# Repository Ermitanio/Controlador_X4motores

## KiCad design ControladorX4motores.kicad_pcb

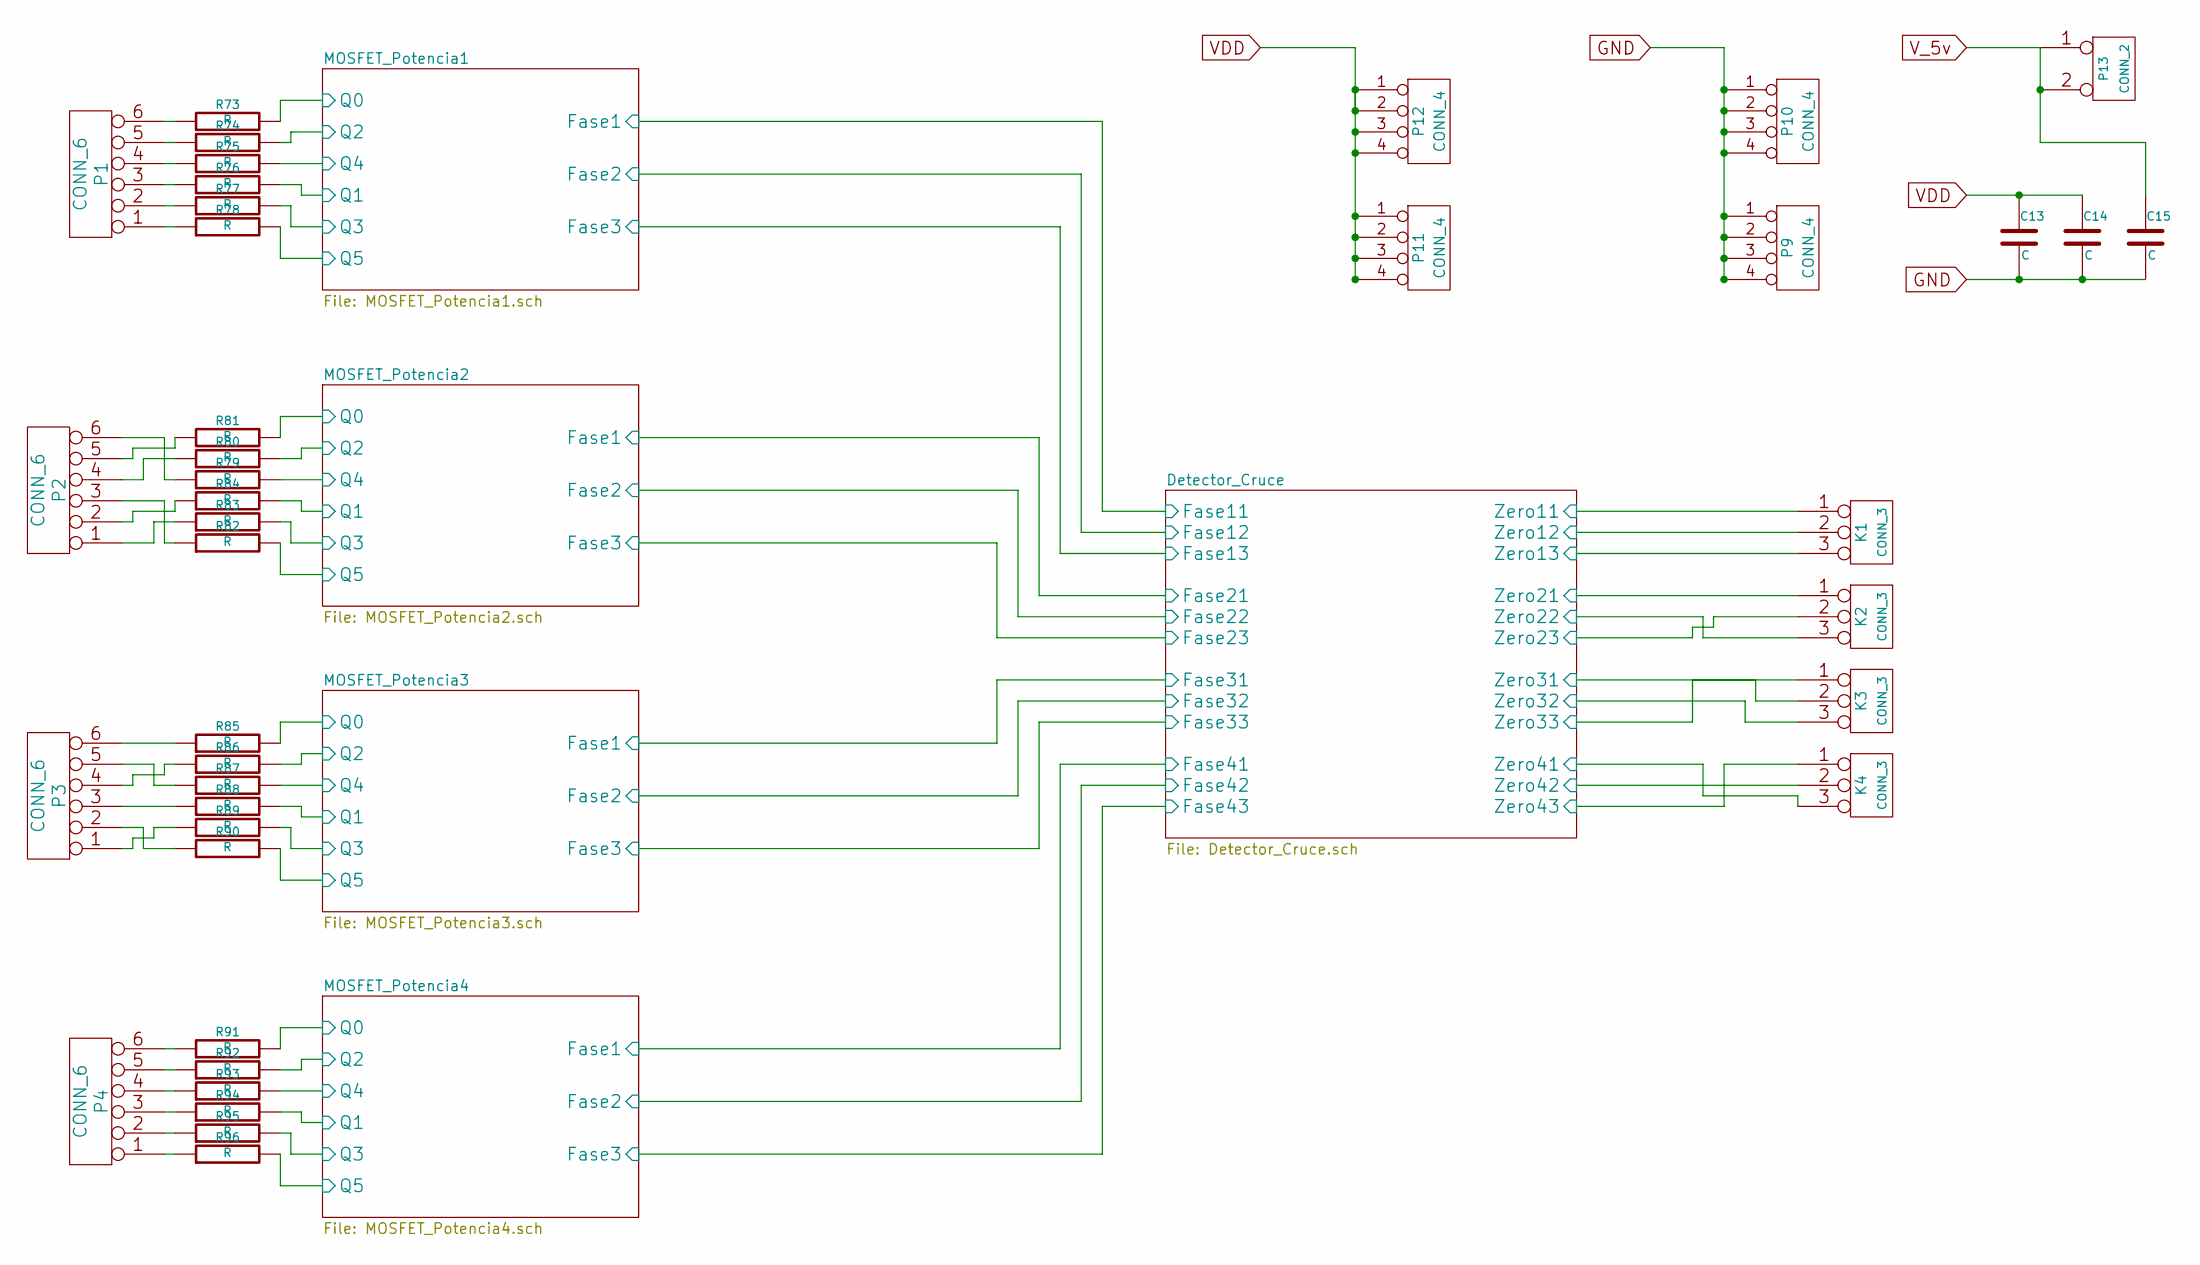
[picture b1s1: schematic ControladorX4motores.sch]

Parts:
C13, C14, C15: C
K1, K2, K3, K4: CONN_3
P1, P2, P3, P4: CONN_6
P9, P10, P11, P12: CONN_4
P13: CONN_2
R73, R74, R75, R76, R77, R78, R79, R80, R81, R82, R83, R84, R85, R86, R87, R88, R89, R90, R91, R92, R93, R94, R95, R96: R

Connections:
/Detector_Cruce/Zero11: K1.1; also elsewhere on the board
/Detector_Cruce/Zero12: K1.2 (PM); also elsewhere on the board
/Detector_Cruce/Zero13: K1.3; also elsewhere on the board
/Detector_Cruce/Zero21: K2.1; also elsewhere on the board
/Detector_Cruce/Zero22: K2.3; also elsewhere on the board
/Detector_Cruce/Zero23: K2.2 (PM); also elsewhere on the board
/Detector_Cruce/Zero31: K3.2 (PM); also elsewhere on the board
/Detector_Cruce/Zero32: K3.3; also elsewhere on the board
/Detector_Cruce/Zero33: K3.1; also elsewhere on the board
/Detector_Cruce/Zero41: K4.3; also elsewhere on the board
/Detector_Cruce/Zero42: K4.2 (PM); also elsewhere on the board
/Detector_Cruce/Zero43: K4.1; also elsewhere on the board
/MOSFET_Potencia1/Q0: R73.2; also elsewhere on the board
/MOSFET_Potencia1/Q1: R76.2; also elsewhere on the board
/MOSFET_Potencia1/Q2: R74.2; also elsewhere on the board
/MOSFET_Potencia1/Q3: R77.2; also elsewhere on the board
/MOSFET_Potencia1/Q4: R75.2; also elsewhere on the board
/MOSFET_Potencia1/Q5: R78.2; also elsewhere on the board
/MOSFET_Potencia2/Q0: R81.2; also elsewhere on the board
/MOSFET_Potencia2/Q1: R84.2; also elsewhere on the board
/MOSFET_Potencia2/Q2: R80.2; also elsewhere on the board
/MOSFET_Potencia2/Q3: R83.2; also elsewhere on the board
/MOSFET_Potencia2/Q4: R79.2; also elsewhere on the board
/MOSFET_Potencia2/Q5: R82.2; also elsewhere on the board
/MOSFET_Potencia3/Q0: R85.2; also elsewhere on the board
/MOSFET_Potencia3/Q1: R88.2; also elsewhere on the board
/MOSFET_Potencia3/Q2: R86.2; also elsewhere on the board
/MOSFET_Potencia3/Q3: R89.2; also elsewhere on the board
/MOSFET_Potencia3/Q4: R87.2; also elsewhere on the board
/MOSFET_Potencia3/Q5: R90.2; also elsewhere on the board
/MOSFET_Potencia4/Q0: R91.2; also elsewhere on the board
/MOSFET_Potencia4/Q1: R94.2; also elsewhere on the board
/MOSFET_Potencia4/Q2: R92.2; also elsewhere on the board
/MOSFET_Potencia4/Q3: R95.2; also elsewhere on the board
/MOSFET_Potencia4/Q4: R93.2; also elsewhere on the board
/MOSFET_Potencia4/Q5: R96.2; also elsewhere on the board
GND: C13.2, C14.2, C15.2, P9.1, P9.2, P9.3, P9.4, P10.1, P10.2, P10.3, P10.4; also elsewhere on the board
unnamed: P4.1, R96.1
unnamed: P4.2, R95.1
unnamed: P4.3, R94.1
unnamed: P4.4, R93.1
unnamed: P4.5, R92.1
unnamed: P4.6, R91.1
unnamed: P3.2, R90.1
unnamed: P3.3, R88.1
unnamed: P3.6, R85.1
unnamed: P1.1, R78.1
unnamed: P1.2, R77.1
unnamed: P1.3, R76.1
unnamed: P1.4, R75.1
unnamed: P1.5, R74.1
unnamed: P1.6, R73.1
unnamed: P3.5, R87.1
unnamed: P3.1, R89.1
unnamed: P3.4, R86.1
unnamed: P2.1, R83.1
unnamed: P2.2, R84.1
unnamed: P2.6, R79.1
unnamed: P2.3, R82.1
unnamed: P2.4, R80.1
unnamed: P2.5, R81.1
VDD: C13.1, C14.1, P11.1, P11.2, P11.3, P11.4, P12.1, P12.2, P12.3, P12.4; also elsewhere on the board
V_5v: C15.1, P13.1, P13.2 (PM); also elsewhere on the board

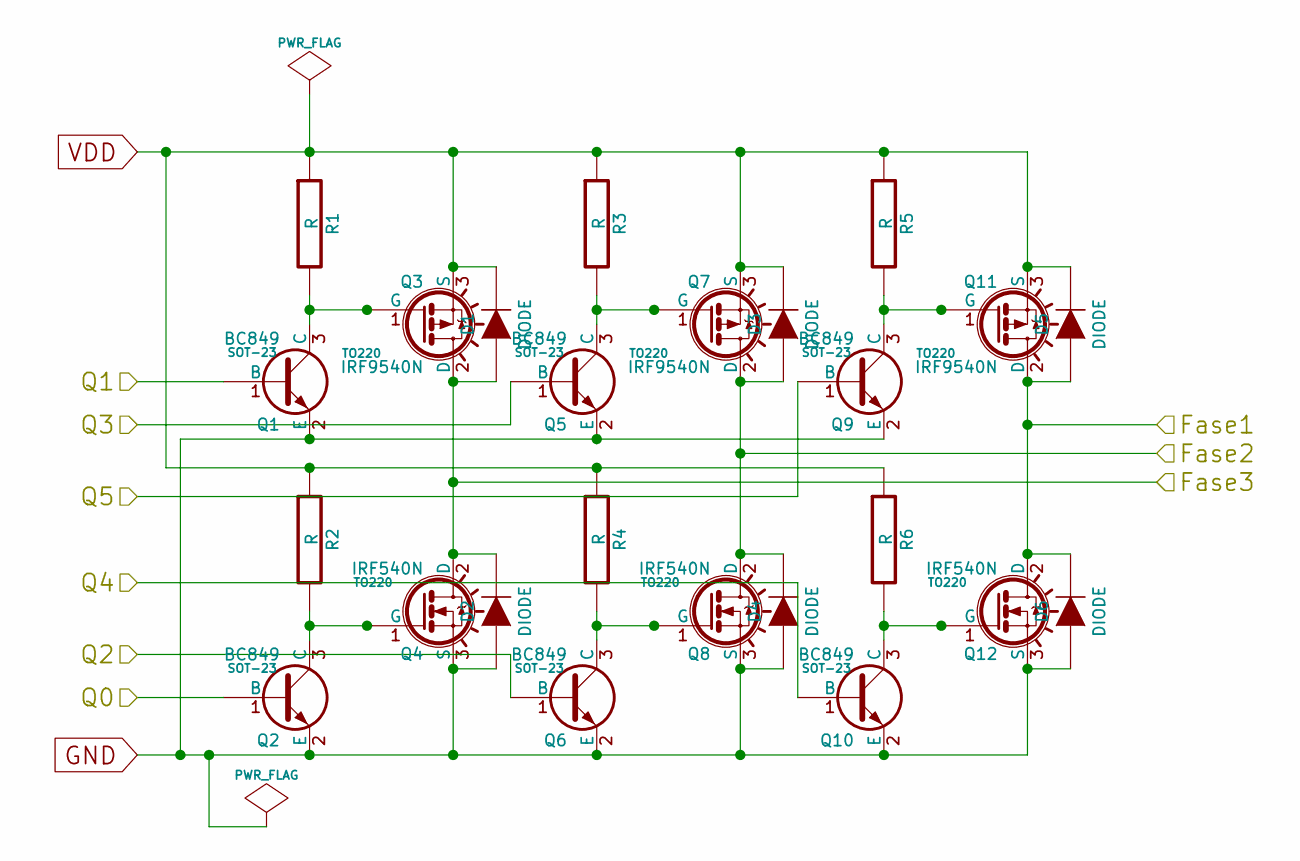
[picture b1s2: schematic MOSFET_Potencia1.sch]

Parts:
D1, D2, D3, D4, D5, D6: DIODE
Q1, Q2, Q5, Q6, Q9, Q10: BC849; SOT-23
Q3, Q7, Q11: IRF9540N; TO220
Q4, Q8, Q12: IRF540N; TO220
R1, R2, R3, R4, R5, R6: R

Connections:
/Detector_Cruce/Fase12: D3.1 (A), D4.2 (K), Q7.2 (D), Q8.2 (D); also elsewhere on the board
/Detector_Cruce/Fase13: D1.1 (A), D2.2 (K), Q3.2 (D), Q4.2 (D); also elsewhere on the board
/MOSFET_Potencia1/Fase1: D5.1 (A), D6.2 (K), Q11.2 (D), Q12.2 (D); also elsewhere on the board
/MOSFET_Potencia1/Q0: Q2.1 (B); also elsewhere on the board
/MOSFET_Potencia1/Q1: Q1.1 (B); also elsewhere on the board
/MOSFET_Potencia1/Q2: Q6.1 (B); also elsewhere on the board
/MOSFET_Potencia1/Q3: Q5.1 (B); also elsewhere on the board
/MOSFET_Potencia1/Q4: Q10.1 (B); also elsewhere on the board
/MOSFET_Potencia1/Q5: Q9.1 (B); also elsewhere on the board
GND: D2.1 (A), D4.1 (A), D6.1 (A), Q1.2 (E), Q2.2 (E), Q4.3 (S), Q5.2 (E), Q6.2 (E), Q8.3 (S), Q9.2 (E), Q10.2 (E), Q12.3 (S); also elsewhere on the board
unnamed: Q5.3 (C), Q7.1 (G), R3.2
unnamed: Q1.3 (C), Q3.1 (G), R1.2
unnamed: Q9.3 (C), Q11.1 (G), R5.2
unnamed: Q6.3 (C), Q8.1 (G), R4.2
unnamed: Q2.3 (C), Q4.1 (G), R2.2
unnamed: Q10.3 (C), Q12.1 (G), R6.2
VDD: D1.2 (K), D3.2 (K), D5.2 (K), Q3.3 (S), Q7.3 (S), Q11.3 (S), R1.1, R2.1, R3.1, R4.1, R5.1, R6.1; also elsewhere on the board

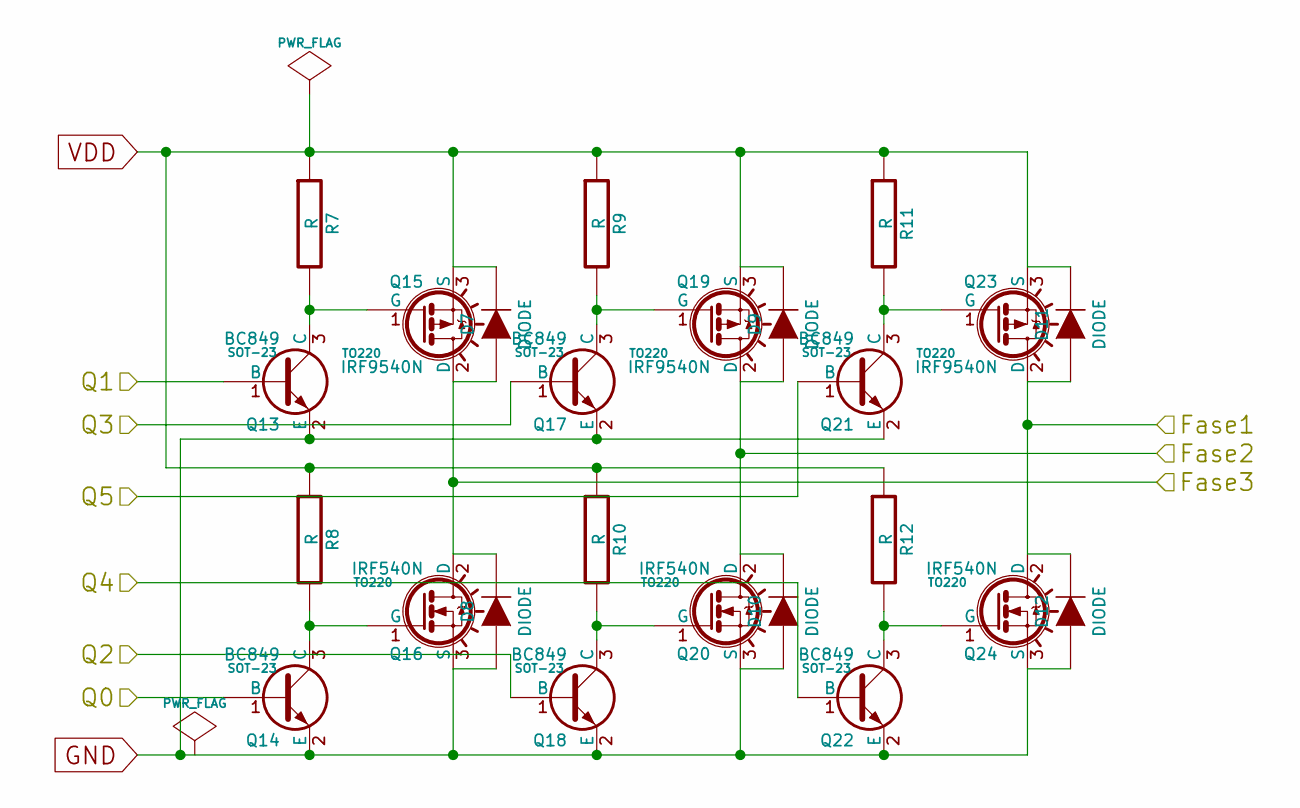
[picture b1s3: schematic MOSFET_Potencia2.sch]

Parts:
D7, D8, D9, D10, D11, D12: DIODE
Q13, Q14, Q17, Q18, Q21, Q22: BC849; SOT-23
Q15, Q19, Q23: IRF9540N; TO220
Q16, Q20, Q24: IRF540N; TO220
R7, R8, R9, R10, R11, R12: R

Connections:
/Detector_Cruce/Fase23: D7.1 (A), D8.2 (K), Q15.2 (D), Q16.2 (D); also elsewhere on the board
/MOSFET_Potencia2/Fase1: D11.1 (A), D12.2 (K), Q23.2 (D), Q24.2 (D); also elsewhere on the board
/MOSFET_Potencia2/Fase2: D9.1 (A), D10.2 (K), Q19.2 (D), Q20.2 (D); also elsewhere on the board
/MOSFET_Potencia2/Q0: Q14.1 (B); also elsewhere on the board
/MOSFET_Potencia2/Q1: Q13.1 (B); also elsewhere on the board
/MOSFET_Potencia2/Q2: Q18.1 (B); also elsewhere on the board
/MOSFET_Potencia2/Q3: Q17.1 (B); also elsewhere on the board
/MOSFET_Potencia2/Q4: Q22.1 (B); also elsewhere on the board
/MOSFET_Potencia2/Q5: Q21.1 (B); also elsewhere on the board
GND: D8.1 (A), D10.1 (A), D12.1 (A), Q13.2 (E), Q14.2 (E), Q16.3 (S), Q17.2 (E), Q18.2 (E), Q20.3 (S), Q21.2 (E), Q22.2 (E), Q24.3 (S); also elsewhere on the board
unnamed: Q18.3 (C), Q20.1 (G), R10.2
unnamed: Q13.3 (C), Q15.1 (G), R7.2
unnamed: Q17.3 (C), Q19.1 (G), R9.2
unnamed: Q22.3 (C), Q24.1 (G), R12.2
unnamed: Q21.3 (C), Q23.1 (G), R11.2
unnamed: Q14.3 (C), Q16.1 (G), R8.2
VDD: D7.2 (K), D9.2 (K), D11.2 (K), Q15.3 (S), Q19.3 (S), Q23.3 (S), R7.1, R8.1, R9.1, R10.1, R11.1, R12.1; also elsewhere on the board

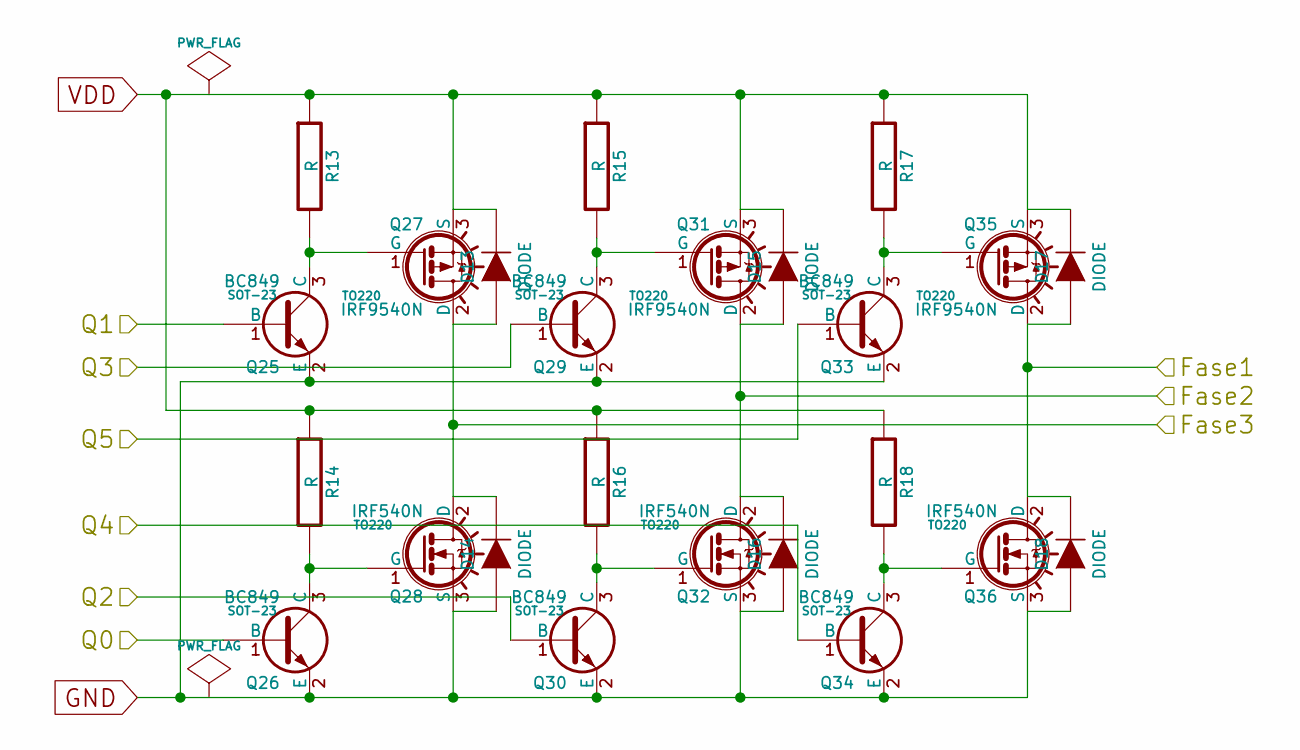
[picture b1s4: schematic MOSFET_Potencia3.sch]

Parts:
D13, D14, D15, D16, D17, D18: DIODE
Q25, Q26, Q29, Q30, Q33, Q34: BC849; SOT-23
Q27, Q31, Q35: IRF9540N; TO220
Q28, Q32, Q36: IRF540N; TO220
R13, R14, R15, R16, R17, R18: R

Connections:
/MOSFET_Potencia3/Fase1: D17.1 (A), D18.2 (K), Q35.2 (D), Q36.2 (D); also elsewhere on the board
/MOSFET_Potencia3/Fase2: D15.1 (A), D16.2 (K), Q31.2 (D), Q32.2 (D); also elsewhere on the board
/MOSFET_Potencia3/Fase3: D13.1 (A), D14.2 (K), Q27.2 (D), Q28.2 (D); also elsewhere on the board
/MOSFET_Potencia3/Q0: Q26.1 (B); also elsewhere on the board
/MOSFET_Potencia3/Q1: Q25.1 (B); also elsewhere on the board
/MOSFET_Potencia3/Q2: Q30.1 (B); also elsewhere on the board
/MOSFET_Potencia3/Q3: Q29.1 (B); also elsewhere on the board
/MOSFET_Potencia3/Q4: Q34.1 (B); also elsewhere on the board
/MOSFET_Potencia3/Q5: Q33.1 (B); also elsewhere on the board
GND: D14.1 (A), D16.1 (A), D18.1 (A), Q25.2 (E), Q26.2 (E), Q28.3 (S), Q29.2 (E), Q30.2 (E), Q32.3 (S), Q33.2 (E), Q34.2 (E), Q36.3 (S); also elsewhere on the board
unnamed: Q33.3 (C), Q35.1 (G), R17.2
unnamed: Q29.3 (C), Q31.1 (G), R15.2
unnamed: Q34.3 (C), Q36.1 (G), R18.2
unnamed: Q30.3 (C), Q32.1 (G), R16.2
unnamed: Q26.3 (C), Q28.1 (G), R14.2
unnamed: Q25.3 (C), Q27.1 (G), R13.2
VDD: D13.2 (K), D15.2 (K), D17.2 (K), Q27.3 (S), Q31.3 (S), Q35.3 (S), R13.1, R14.1, R15.1, R16.1, R17.1, R18.1; also elsewhere on the board

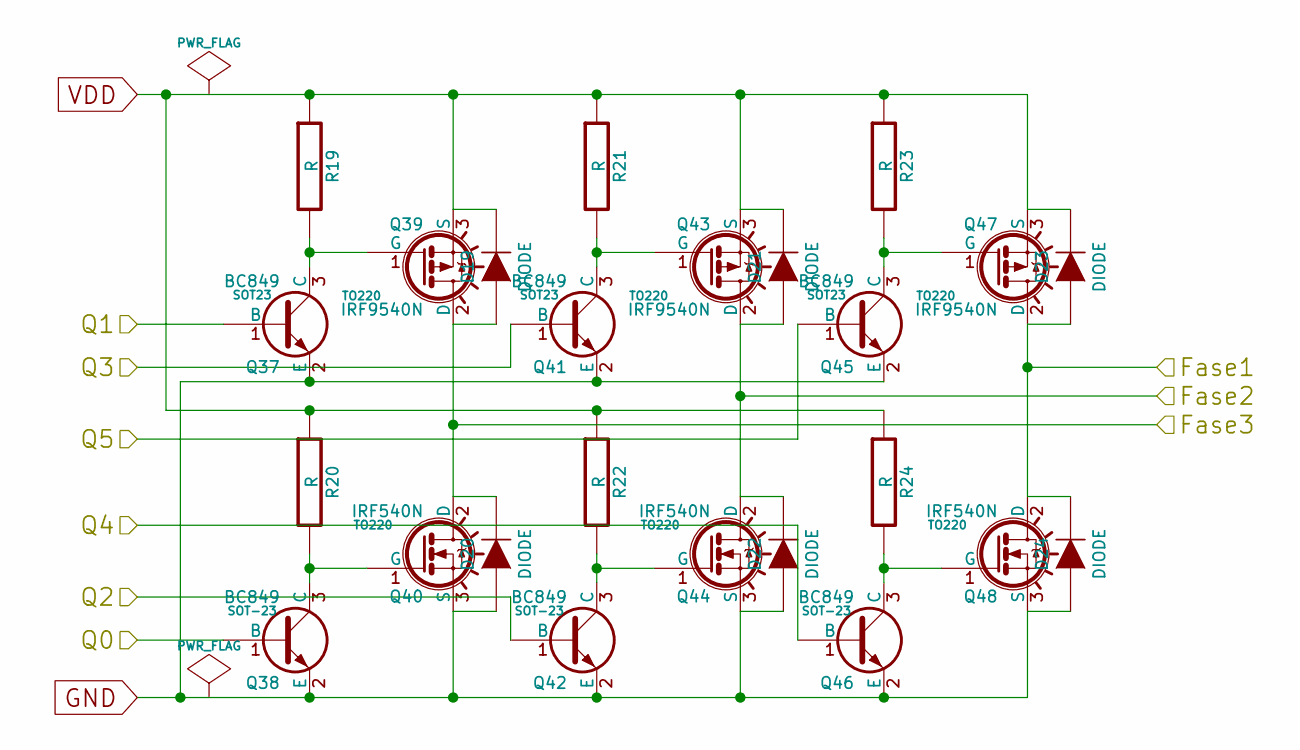
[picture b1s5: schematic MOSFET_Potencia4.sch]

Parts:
D19, D20, D21, D22, D23, D24: DIODE
Q37, Q41, Q45: BC849; SOT23
Q38, Q42, Q46: BC849; SOT-23
Q39, Q43, Q47: IRF9540N; TO220
Q40, Q44, Q48: IRF540N; TO220
R19, R20, R21, R22, R23, R24: R

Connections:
/MOSFET_Potencia4/Fase1: D23.1 (A), D24.2 (K), Q47.2 (D), Q48.2 (D); also elsewhere on the board
/MOSFET_Potencia4/Fase2: D21.1 (A), D22.2 (K), Q43.2 (D), Q44.2 (D); also elsewhere on the board
/MOSFET_Potencia4/Fase3: D19.1 (A), D20.2 (K), Q39.2 (D), Q40.2 (D); also elsewhere on the board
/MOSFET_Potencia4/Q0: Q38.1 (B); also elsewhere on the board
/MOSFET_Potencia4/Q1: Q37.1 (B); also elsewhere on the board
/MOSFET_Potencia4/Q2: Q42.1 (B); also elsewhere on the board
/MOSFET_Potencia4/Q3: Q41.1 (B); also elsewhere on the board
/MOSFET_Potencia4/Q4: Q46.1 (B); also elsewhere on the board
/MOSFET_Potencia4/Q5: Q45.1 (B); also elsewhere on the board
GND: D20.1 (A), D22.1 (A), D24.1 (A), Q37.2 (E), Q38.2 (E), Q40.3 (S), Q41.2 (E), Q42.2 (E), Q44.3 (S), Q45.2 (E), Q46.2 (E), Q48.3 (S); also elsewhere on the board
unnamed: Q37.3 (C), Q39.1 (G), R19.2
unnamed: Q41.3 (C), Q43.1 (G), R21.2
unnamed: Q38.3 (C), Q40.1 (G), R20.2
unnamed: Q46.3 (C), Q48.1 (G), R24.2
unnamed: Q45.3 (C), Q47.1 (G), R23.2
unnamed: Q42.3 (C), Q44.1 (G), R22.2
VDD: D19.2 (K), D21.2 (K), D23.2 (K), Q39.3 (S), Q43.3 (S), Q47.3 (S), R19.1, R20.1, R21.1, R22.1, R23.1, R24.1; also elsewhere on the board

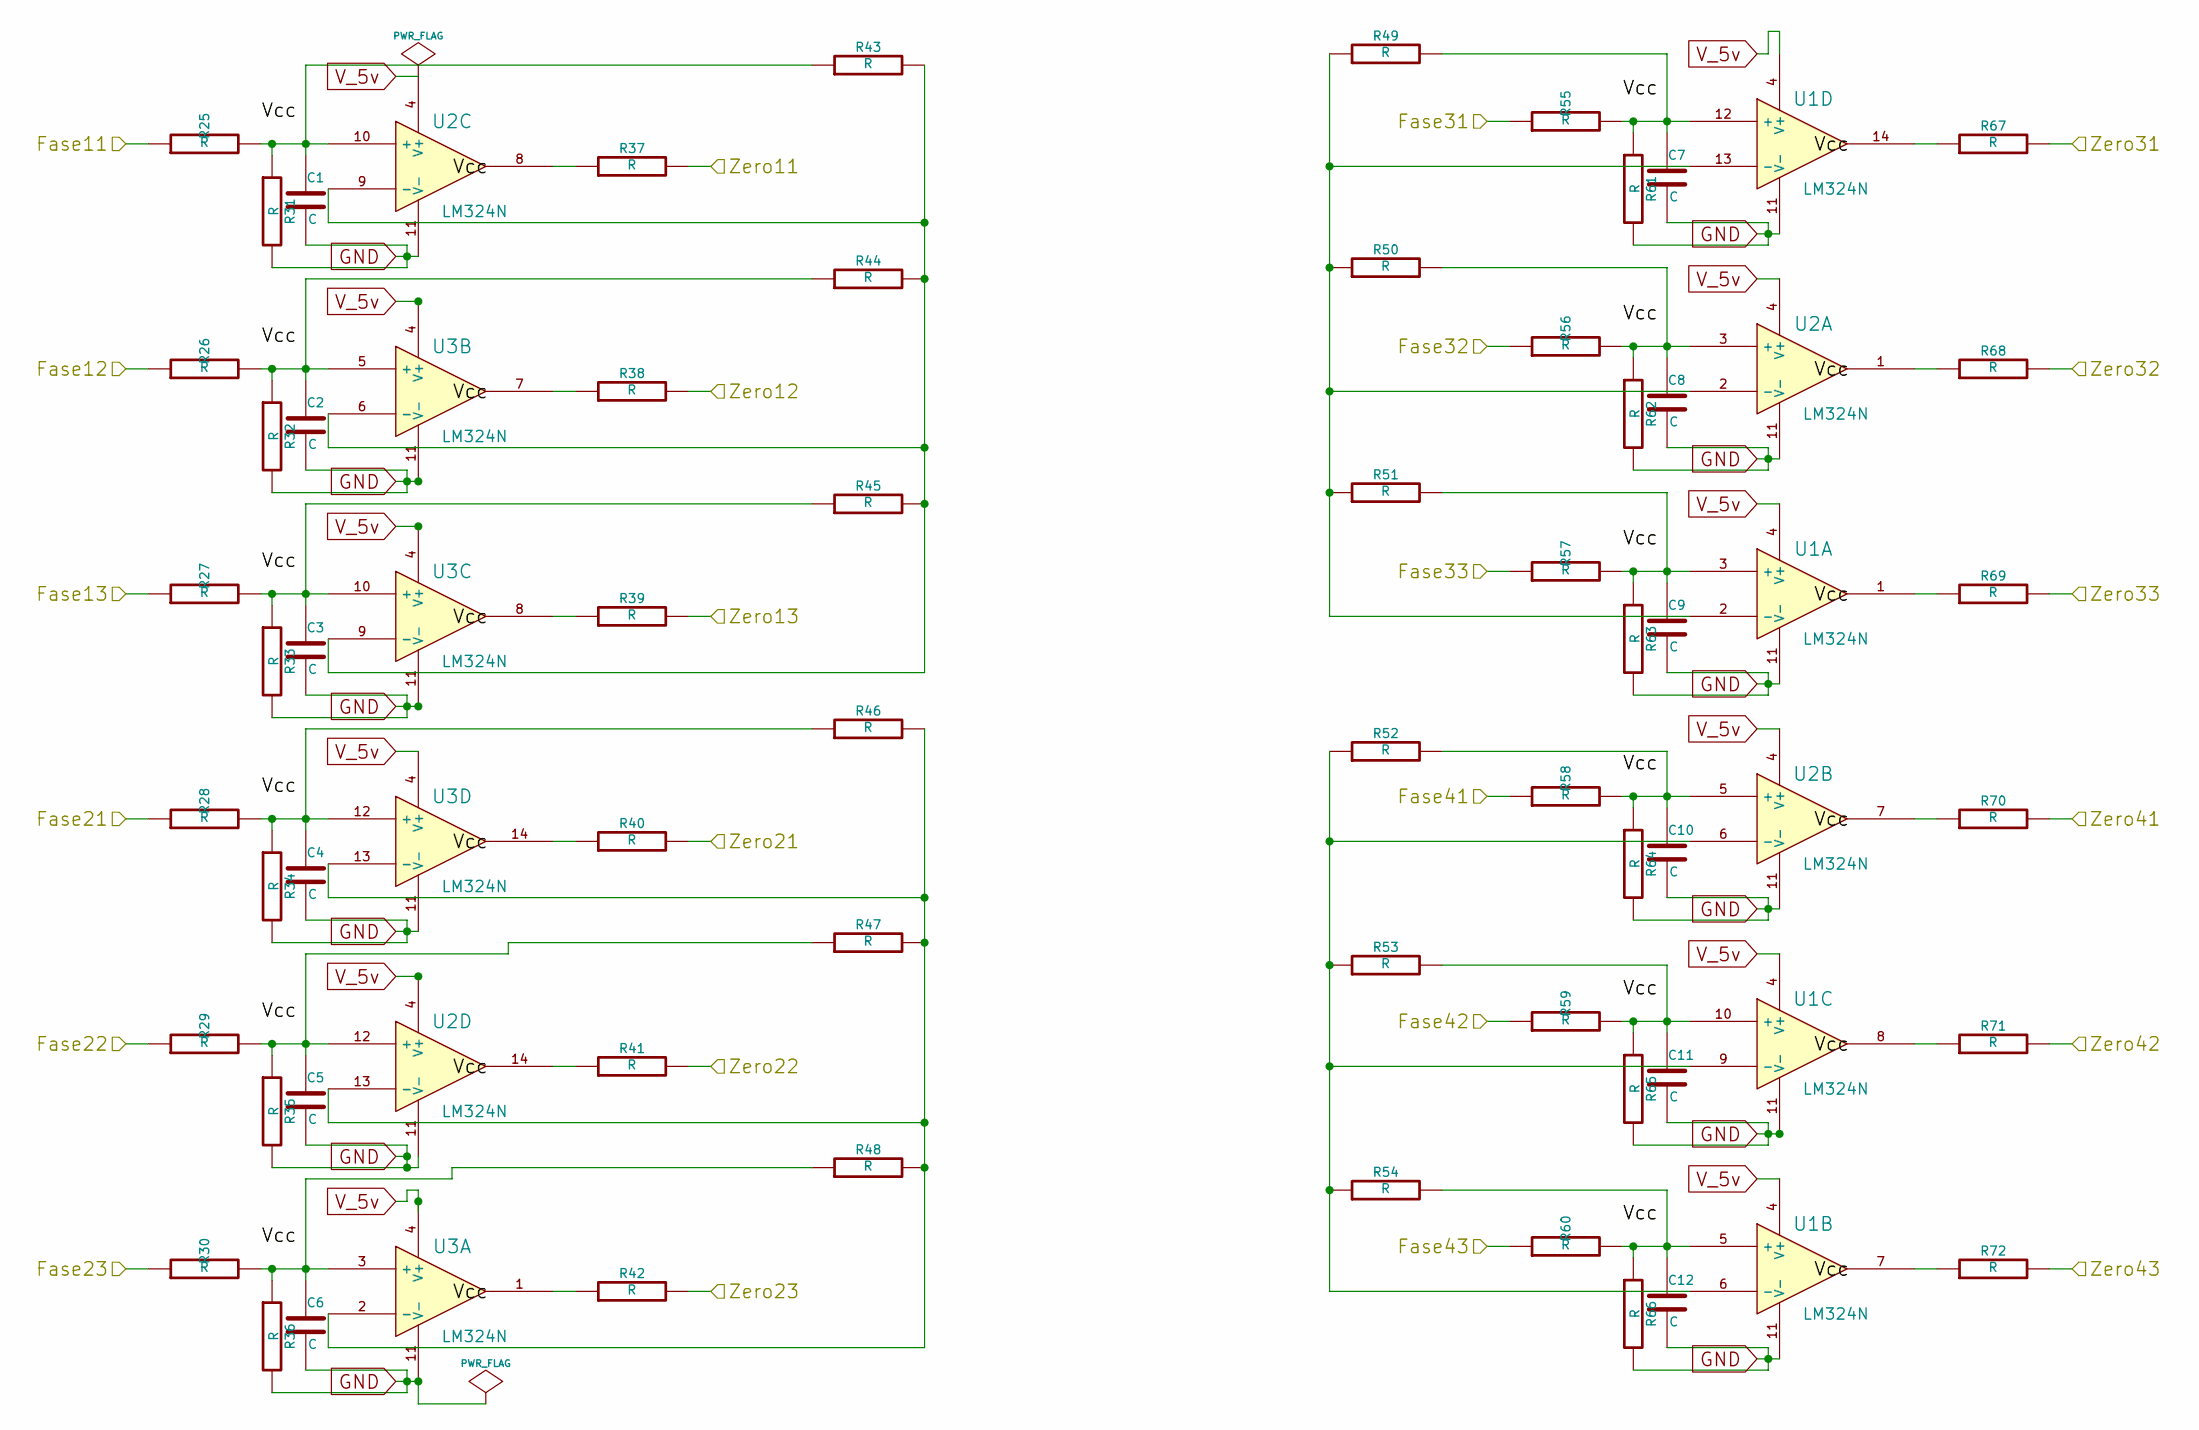
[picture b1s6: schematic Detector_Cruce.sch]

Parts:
C1, C2, C3, C4, C5, C6, C7, C8, C9, C10, C11, C12: C
R25, R26, R27, R28, R29, R30, R31, R32, R33, R34, R35, R36, R37, R38, R39, R40, R41, R42, R43, R44, R45, R46, R47, R48, R49, R50, R51, R52, R53, R54, R55, R56, R57, R58, R59, R60, R61, R62, R63, R64, R65, R66, R67, R68, R69, R70, R71, R72: R
U1, U2, U3: LM324N

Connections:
/Detector_Cruce/Fase12: R26.1; also elsewhere on the board
/Detector_Cruce/Fase13: R27.1; also elsewhere on the board
/Detector_Cruce/Fase23: R30.1; also elsewhere on the board
/Detector_Cruce/Zero11: R37.2; also elsewhere on the board
/Detector_Cruce/Zero12: R38.2; also elsewhere on the board
/Detector_Cruce/Zero13: R39.2; also elsewhere on the board
/Detector_Cruce/Zero21: R40.2; also elsewhere on the board
/Detector_Cruce/Zero22: R41.2; also elsewhere on the board
/Detector_Cruce/Zero23: R42.2; also elsewhere on the board
/Detector_Cruce/Zero31: R67.2; also elsewhere on the board
/Detector_Cruce/Zero32: R68.2; also elsewhere on the board
/Detector_Cruce/Zero33: R69.2; also elsewhere on the board
/Detector_Cruce/Zero41: R70.2; also elsewhere on the board
/Detector_Cruce/Zero42: R71.2; also elsewhere on the board
/Detector_Cruce/Zero43: R72.2; also elsewhere on the board
/MOSFET_Potencia1/Fase1: R25.1; also elsewhere on the board
/MOSFET_Potencia2/Fase1: R28.1; also elsewhere on the board
/MOSFET_Potencia2/Fase2: R29.1; also elsewhere on the board
/MOSFET_Potencia3/Fase1: R55.1; also elsewhere on the board
/MOSFET_Potencia3/Fase2: R56.1; also elsewhere on the board
/MOSFET_Potencia3/Fase3: R57.1; also elsewhere on the board
/MOSFET_Potencia4/Fase1: R58.1; also elsewhere on the board
/MOSFET_Potencia4/Fase2: R59.1; also elsewhere on the board
/MOSFET_Potencia4/Fase3: R60.1; also elsewhere on the board
GND: C1.2, C2.2, C3.2, C4.2, C5.2, C6.2, C7.2, C8.2, C9.2, C10.2, C11.2, C12.2, R31.2, R32.2, R33.2, R34.2, R35.2, R36.2, R61.2, R62.2, R63.2, R64.2, R65.2, R66.2, U1.11 (V-), U2.11 (V-), U3.11 (V-); also elsewhere on the board
unnamed: R49.1, R50.1, R51.1, U1.2 (-), U1.13 (-), U2.2 (-)
unnamed: C1.1, R25.2, R31.1, R43.1, U2.10 (+)
unnamed: R43.2, R44.2, R45.2, U2.9 (-), U3.6 (-), U3.9 (-)
unnamed: C5.1, R29.2, R35.1, R47.1, U2.12 (+)
unnamed: C4.1, R28.2, R34.1, R46.1, U3.12 (+)
unnamed: R40.1, U3.14
unnamed: R41.1, U2.14
unnamed: C6.1, R30.2, R36.1, R48.1, U3.3 (+)
unnamed: R42.1, U3.1
unnamed: C2.1, R26.2, R32.1, R44.1, U3.5 (+)
unnamed: R38.1, U3.7
unnamed: R37.1, U2.8
unnamed: C3.1, R27.2, R33.1, R45.1, U3.10 (+)
unnamed: R39.1, U3.8
unnamed: C8.1, R50.2, R56.2, R62.1, U2.3 (+)
unnamed: R46.2, R47.2, R48.2, U2.13 (-), U3.2 (-), U3.13 (-)
unnamed: R70.1, U2.7
unnamed: R69.1, U1.1
unnamed: R67.1, U1.14
unnamed: R72.1, U1.7
unnamed: R71.1, U1.8
unnamed: R68.1, U2.1
unnamed: R52.1, R53.1, R54.1, U1.6 (-), U1.9 (-), U2.6 (-)
unnamed: C10.1, R52.2, R58.2, R64.1, U2.5 (+)
unnamed: C11.1, R53.2, R59.2, R65.1, U1.10 (+)
unnamed: C7.1, R49.2, R55.2, R61.1, U1.12 (+)
unnamed: C12.1, R54.2, R60.2, R66.1, U1.5 (+)
unnamed: C9.1, R51.2, R57.2, R63.1, U1.3 (+)
V_5v: U1.4 (V+), U2.4 (V+), U3.4 (V+); also elsewhere on the board

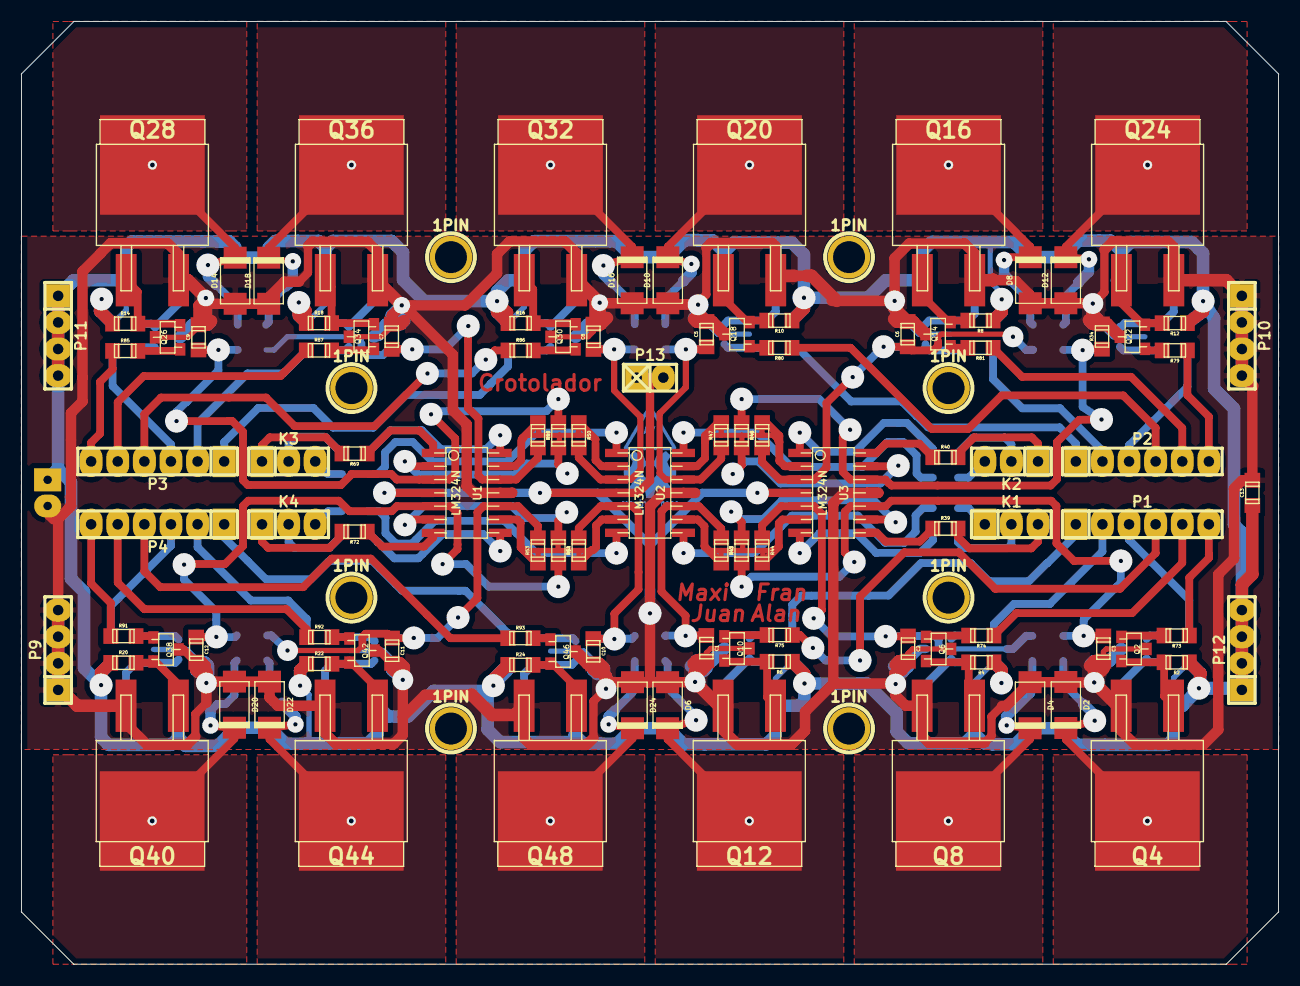
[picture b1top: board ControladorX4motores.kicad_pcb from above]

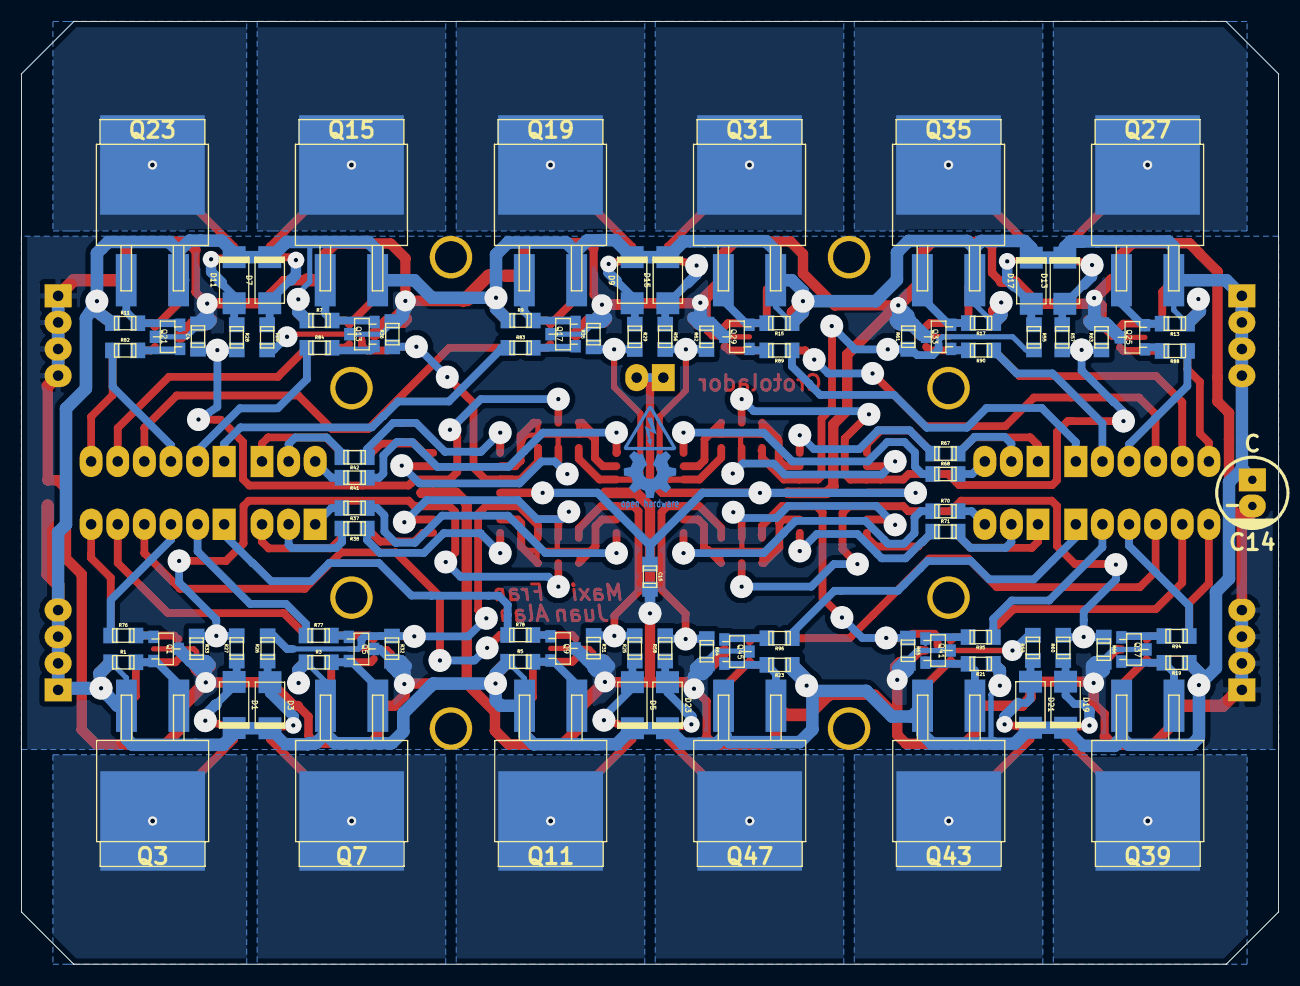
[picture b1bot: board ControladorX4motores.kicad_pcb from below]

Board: 2 copper layers, 120.0 x 90.0 mm, 207 parts (94 on the bottom side), 127 nets.

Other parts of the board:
1PIN, 1PIN#2, 1PIN#3, 1PIN#4, 1PIN#5, 1PIN#6, 1PIN#7, 1PIN#8: P***; 1pin

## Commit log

2015-10-11 :confetti_ball: Added .gitattributes & .gitignore files
2015-10-11 Diseño definitivo motor
    Controlador de cuatro motores, diseño implementado en pcb
